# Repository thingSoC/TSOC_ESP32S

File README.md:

# TSOC_ESP32S - thingSoC Wi-Fi Radio Module :

[TSOC_ESP32S](https://github.com/thingSoC/TSOC_ESP32S)

---------------------------------------

## TSOC_ESP32S Status <a name="TSOC_ESP32S_status"/>

**11/06/2016:** 
Revision 1.0 - Initial Layout released to OSHpark

---------------------------------------
## TSOC_ESP32S Model Images

[TSOC_ESP32S](https://github.com/thingSoC/TSOC_ESP32S)

[TSOC_ESP32S](https://github.com/thingSoC/TSOC_ESP32S)

---------------------------------------

## TSOC_ESP32S Documentation Index <a name="TSOC_ESP32S_documentation_index"/>

[TSOC_ESP32S Project](http://thingsoc.github.io/projects/TSOC_ESP32S.html)

[TSOC_ESP32S Hardware](https://github.com/thingSoC/TSOC_ESP32S/tree/master/TSOC_ESP32S/hardware)

---------------------------------------

## thingSoC Documentation Index <a name="thingSoC_documentation_index"/>

[thingSoC Organization Website](http://thingSoC.github.io)

[thingSoC FAQ - Frequently Asked Questions](http://thingsoc.github.io/support/faq.html)

---------------------------------------

[ 
*thingSoC*](http://thingsoc.github.io)

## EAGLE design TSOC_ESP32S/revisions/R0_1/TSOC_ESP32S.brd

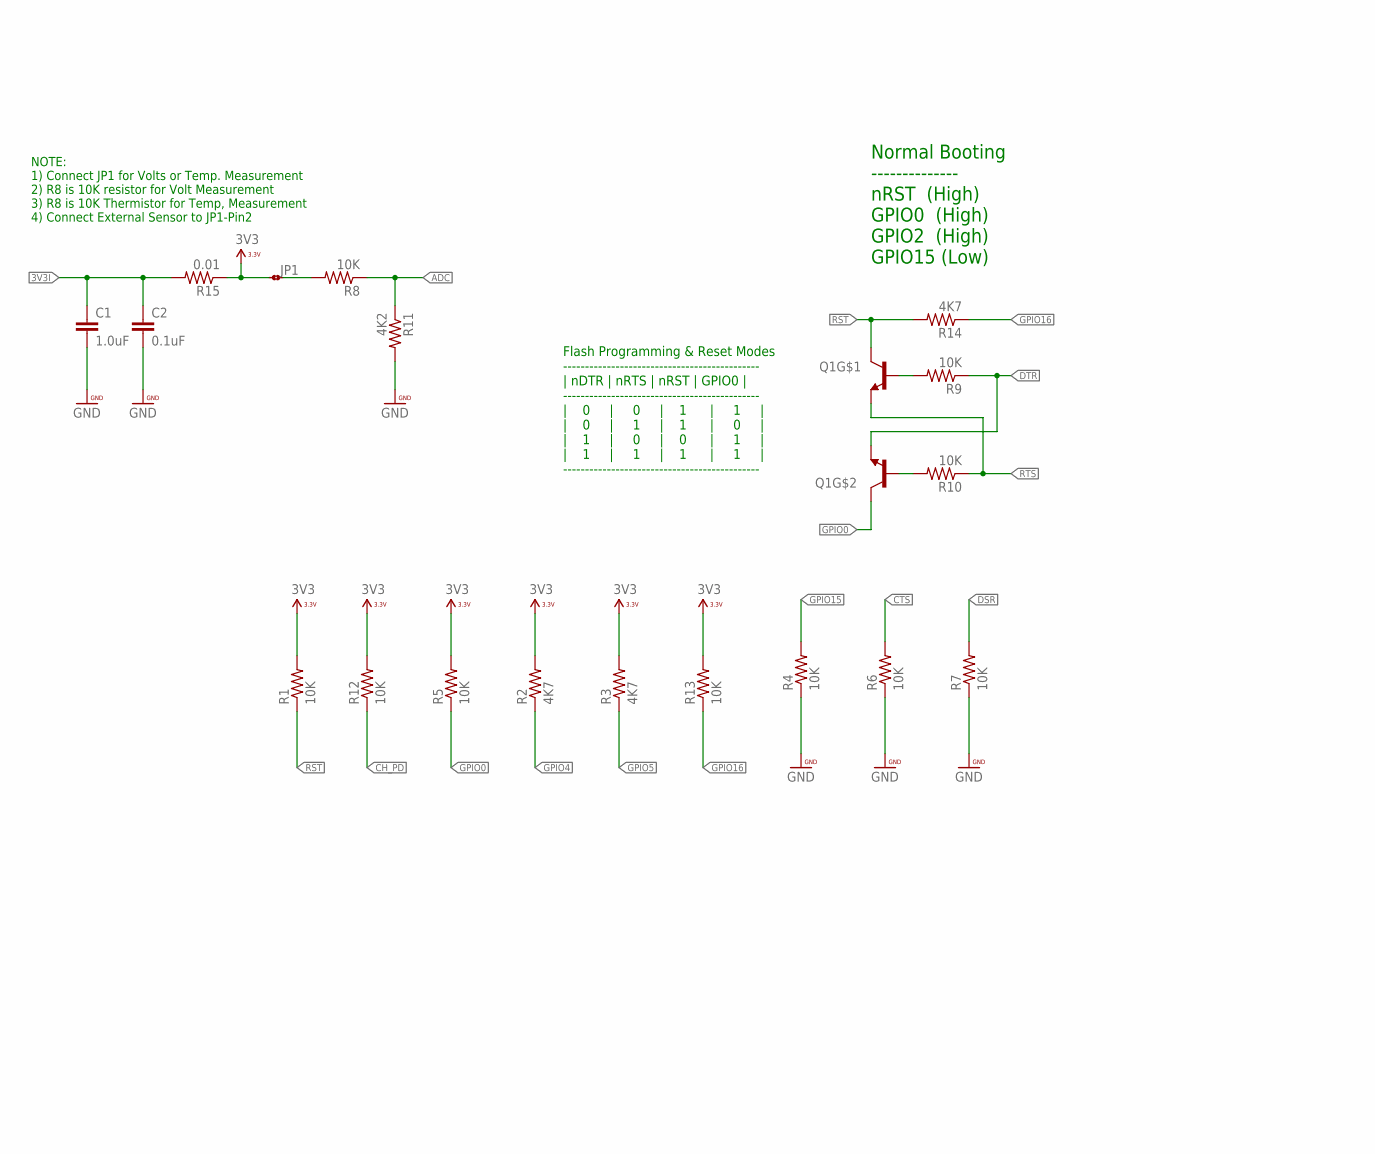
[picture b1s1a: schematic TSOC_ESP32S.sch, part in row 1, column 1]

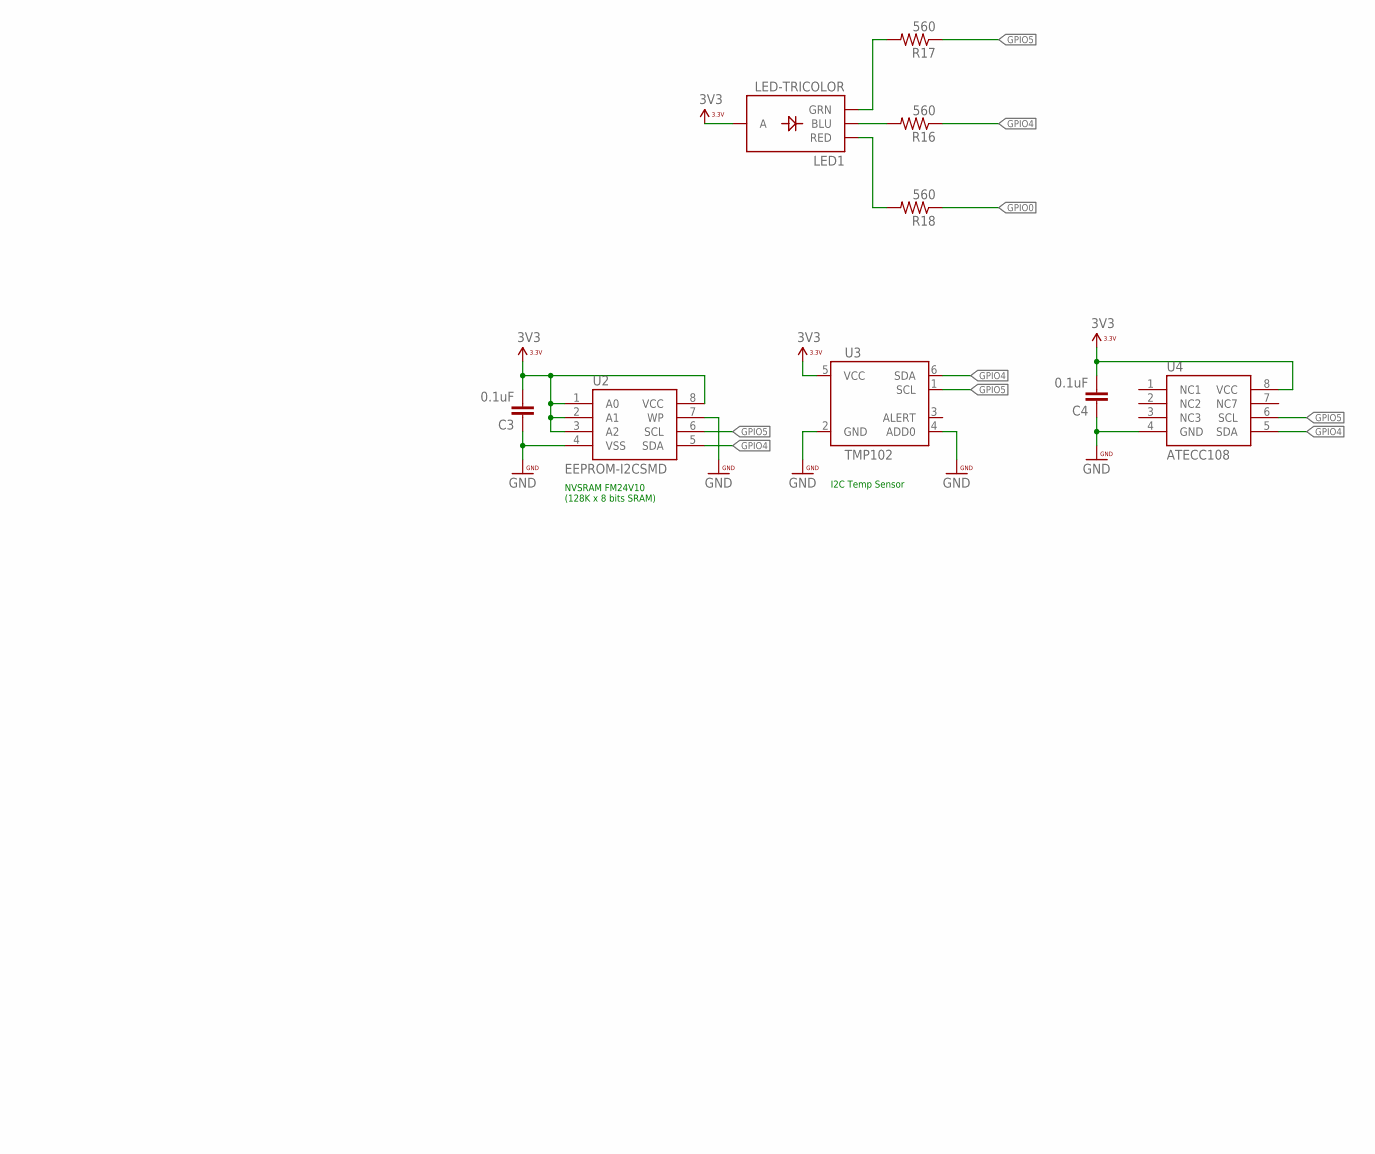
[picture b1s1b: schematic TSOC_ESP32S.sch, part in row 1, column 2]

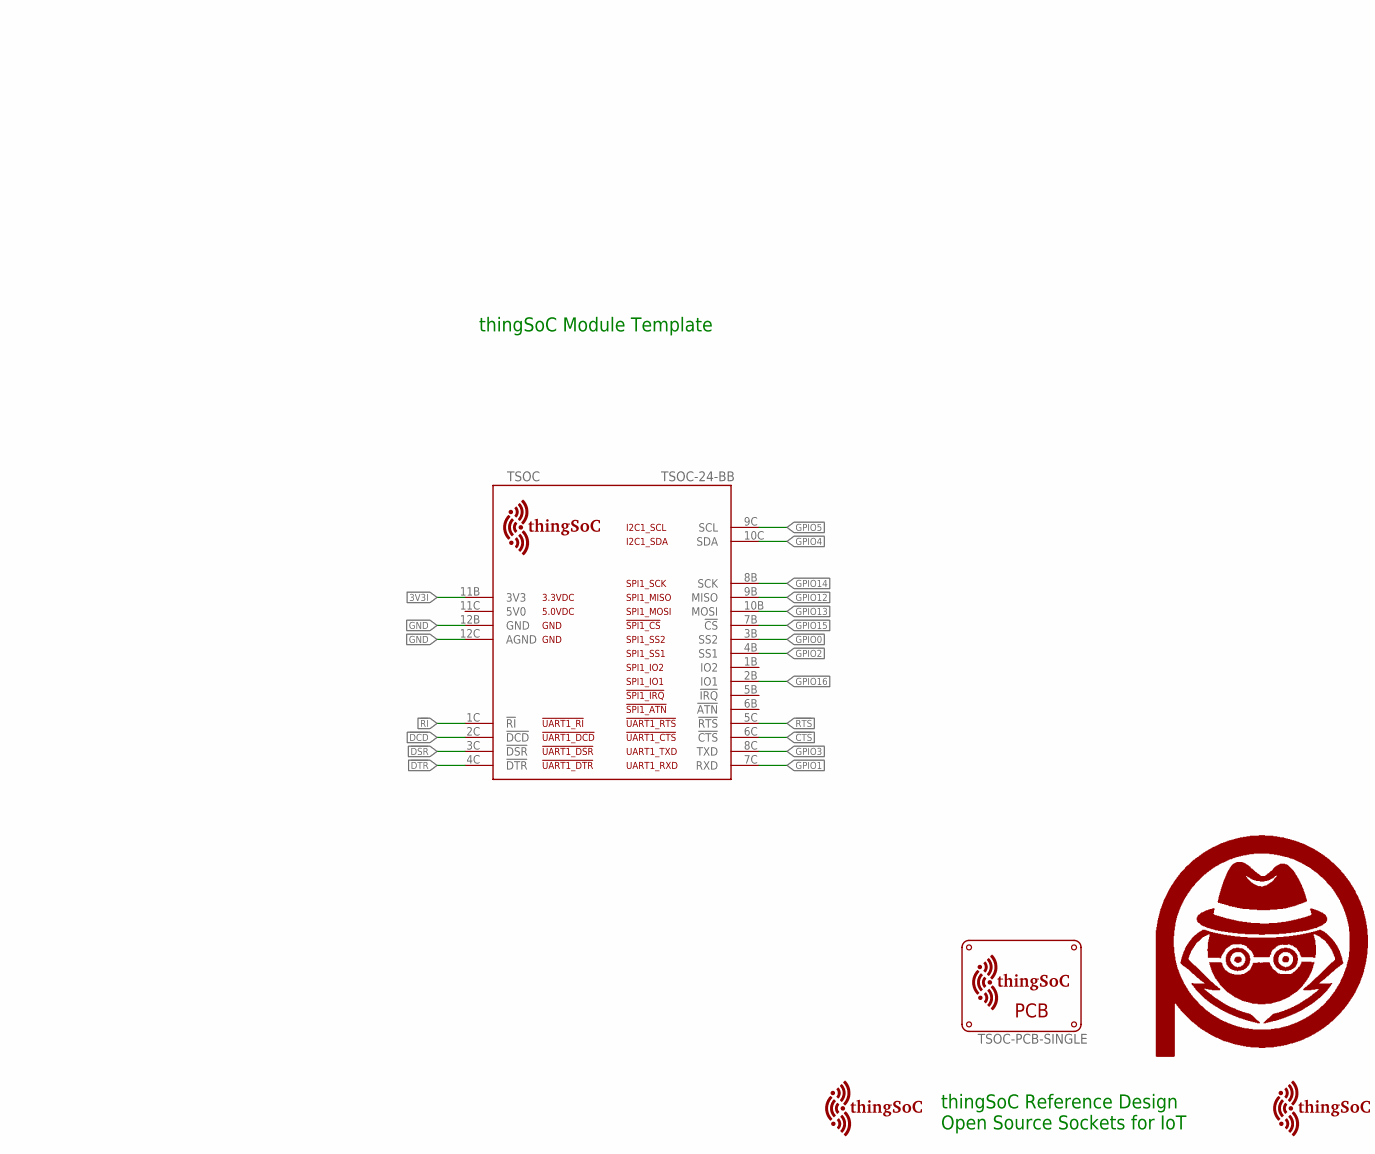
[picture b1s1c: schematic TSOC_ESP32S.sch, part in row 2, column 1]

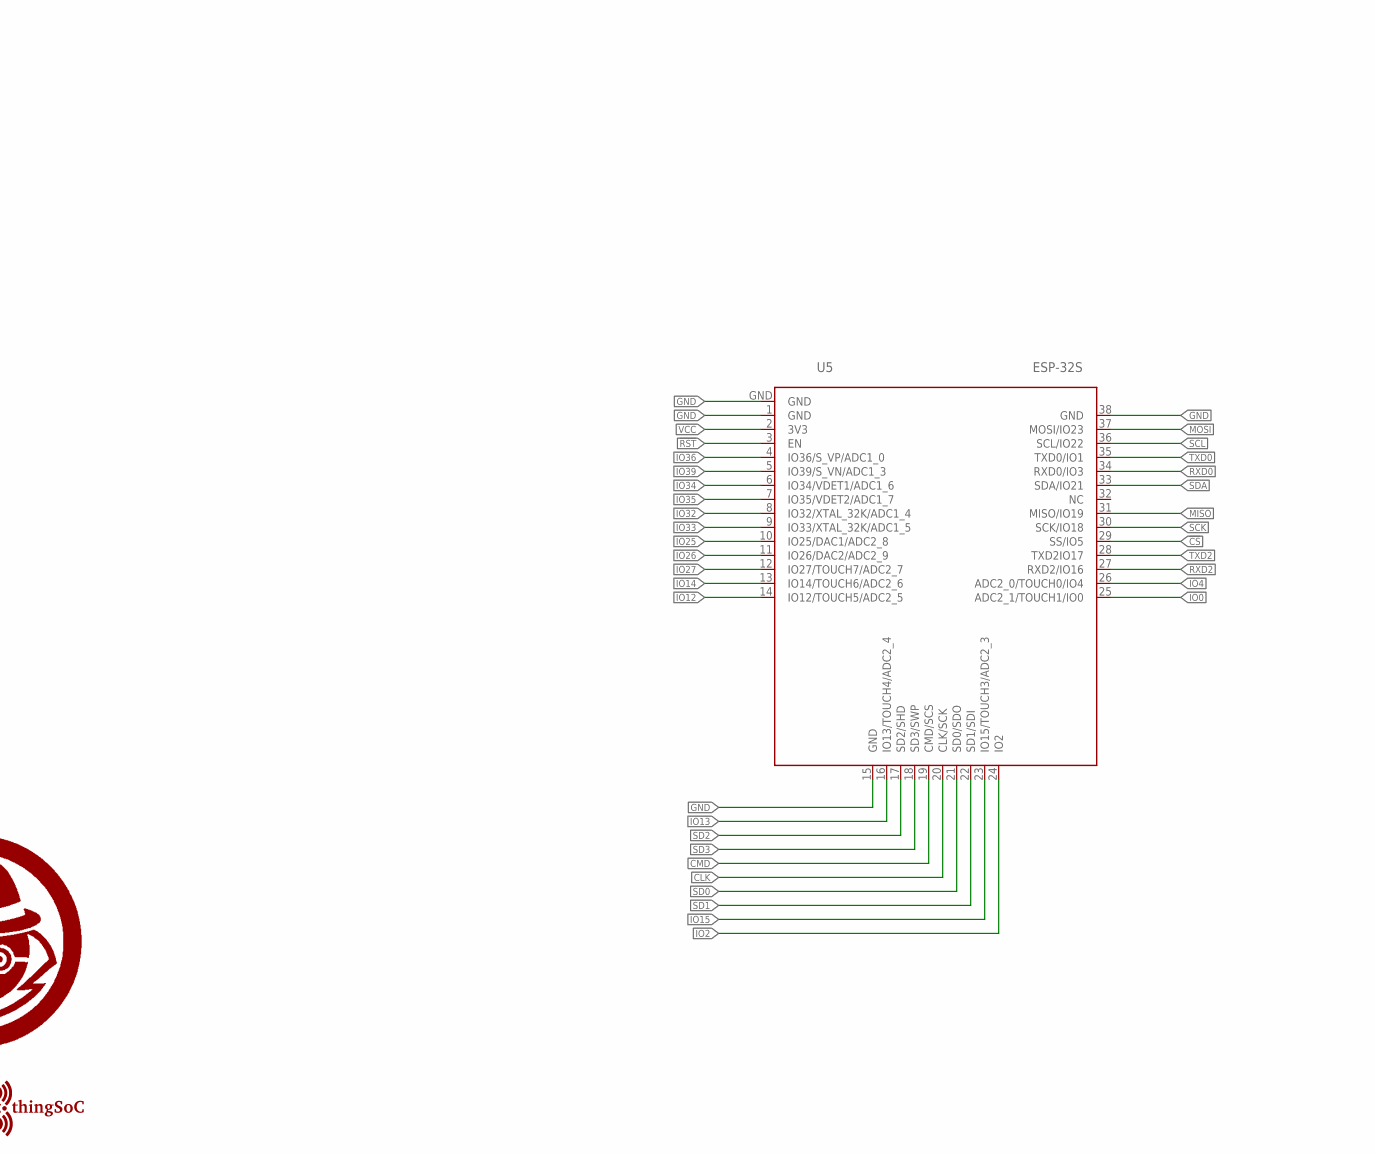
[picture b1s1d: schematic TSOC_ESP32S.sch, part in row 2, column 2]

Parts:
C1: 1.0uF; 0402-CAP
C2, C3, C4: 0.1uF; 0402-CAP
JP1: JMP-2-NO-0402
LED1: LED-TRICOLOR; LED-TRICOLOR-SMD
Q1: MMBT2222A; SOT363
R1, R4, R5, R6, R7, R8, R9, R10, R12, R13: 10K; 0402-RES
R2, R3, R14: 4K7; 0402-RES
R11: 4K2; 0402-RES
R15: 0.01; 0402-RES
R16, R17, R18: 560; 0402-RES
TSOC: TSOC-24-BB; TSOC-BB-S24
U2: EEPROM-I2CSMD; SO08
U3: TMP102; SOT563
U4: ATECC108; SOIC8
U5: ESP-32S
U$11: PA_LOGO_SYMMED; PA_LOGO_AGENT_MED_SYM
U$19, U$20: TSOC-LOGO-MED
U$25: TSOC-PCB-SINGLE; TSOC-BB-BRD-DIM

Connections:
3V3: C3.2, C4.2, JP1.1, LED1.A, R1.2, R2.2, R3.2, R5.2, R12.2, R13.2, R15.1, U2.1 (A0), U2.2 (A1), U2.3 (A2), U2.8 (VCC), U3.5 (VCC), U4.8 (VCC)
3V3I: C1.1, C2.1, R15.2, TSOC.11B (3V3)
!CS: U5.29 (SS/IO5)
!CTS: R6.2, TSOC.6C (!CTS)
!DCD: TSOC.2C (!DCD)
!DSR: R7.2, TSOC.3C (!DSR)
!DTR: Q1.1 (E), R9.1, TSOC.4C (!DTR)
!RI: TSOC.1C (!RI)
!RST: Q1.3 (C), R1.1, R14.2, U5.3 (EN)
!RTS: Q1.4 (E), R10.1, TSOC.5C (!RTS)
ADC: R8.1, R11.1
ADC_RAW: JP1.2, R8.2
BLU: LED1.B (BLU), R16.2
CH_PD: R12.1
CLK: U5.20 (CLK/SCK)
CMD: U5.19 (CMD/SCS)
GND: C1.2, C2.2, C3.1, C4.1, R4.1, R6.1, R7.1, R11.2, TSOC.12B (GND), TSOC.12C (AGND), U2.4 (VSS), U2.7 (WP), U3.2 (GND), U3.4 (ADD0), U4.4 (GND), U5.1 (GND), U5.15 (GND), U5.38 (GND), U5.GND
GPIO0: Q1.6 (C), R5.1, R18.1, TSOC.3B (SS2)
GPIO1: TSOC.7C (RXD)
GPIO2: TSOC.4B (SS1)
GPIO3: TSOC.8C (TXD)
GPIO4: R2.1, R16.1, TSOC.10C (SDA), U2.5 (SDA), U3.6 (SDA), U4.5 (SDA)
GPIO5: R3.1, R17.1, TSOC.9C (SCL), U2.6 (SCL), U3.1 (SCL), U4.6 (SCL)
GPIO12: TSOC.9B (MISO)
GPIO13: TSOC.10B (MOSI)
GPIO14: TSOC.8B (SCK)
GPIO15: R4.2, TSOC.7B (!CS)
GPIO16: R13.1, R14.1, TSOC.2B (IO1)
GRN: LED1.G (GRN), R17.2
IO0: U5.25 (ADC2_1/TOUCH1/IO0)
IO2: U5.24 (IO2)
IO4: U5.26 (ADC2_0/TOUCH0/IO4)
IO12: U5.14 (IO12/TOUCH5/ADC2_5)
IO13: U5.16 (IO13/TOUCH4/ADC2_4)
IO14: U5.13 (IO14/TOUCH6/ADC2_6)
IO15: U5.23 (IO15/TOUCH3/ADC2_3)
IO25: U5.10 (IO25/DAC1/ADC2_8)
IO26: U5.11 (IO26/DAC2/ADC2_9)
IO27: U5.12 (IO27/TOUCH7/ADC2_7)
IO32: U5.8 (IO32/XTAL_32K/ADC1_4)
IO33: U5.9 (IO33/XTAL_32K/ADC1_5)
IO34: U5.6 (IO34/VDET1/ADC1_6)
IO35: U5.7 (IO35/VDET2/ADC1_7)
IO36: U5.4 (IO36/S_VP/ADC1_0)
IO39: U5.5 (IO39/S_VN/ADC1_3)
MISO: U5.31 (MISO/IO19)
MOSI: U5.37 (MOSI/IO23)
unnamed: Q1.5 (B), R9.2
unnamed: Q1.2 (B), R10.2
RED: LED1.R (RED), R18.2
RXD0: U5.34 (RXD0/IO3)
RXD2: U5.27 (RXD2/IO16)
SCK: U5.30 (SCK/IO18)
SCL: U5.36 (SCL/IO22)
SD0: U5.21 (SD0/SDO)
SD1: U5.22 (SD1/SDI)
SD2: U5.17 (SD2/SHD)
SD3: U5.18 (SD3/SWP)
SDA: U5.33 (SDA/IO21)
TXD0: U5.35 (TXD0/IO1)
TXD2: U5.28 (TXD2IO17)
VCC: U5.2 (3V3)

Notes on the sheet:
thingSoC Reference Design Open Source Sockets for IoT
thingSoC Module Template
Normal Booting -------------- nRST (High) GPIO0 (High) GPIO2 (High) GPIO15 (Low)
Flash Programming & Reset Modes --------------------------------------------- | nDTR | nRTS | nRST | GPIO0 | --------------------------------------------- | 0 | 0 | 1 | 1 | | 0 | 1 | 1 | 0 | | 1 | 0 | 0 | 1 | | 1 | 1 | 1 | 1 | ---------------------------------------------
NOTE: 1) Connect JP1 for Volts or Temp. Measurement 2) R8 is 10K resistor for Volt Measurement 3) R8 is 10K Thermistor for Temp, Measurement 4) Connect External Sensor to JP1-Pin2
NVSRAM FM24V10 (128K x 8 bits SRAM)
I2C Temp Sensor

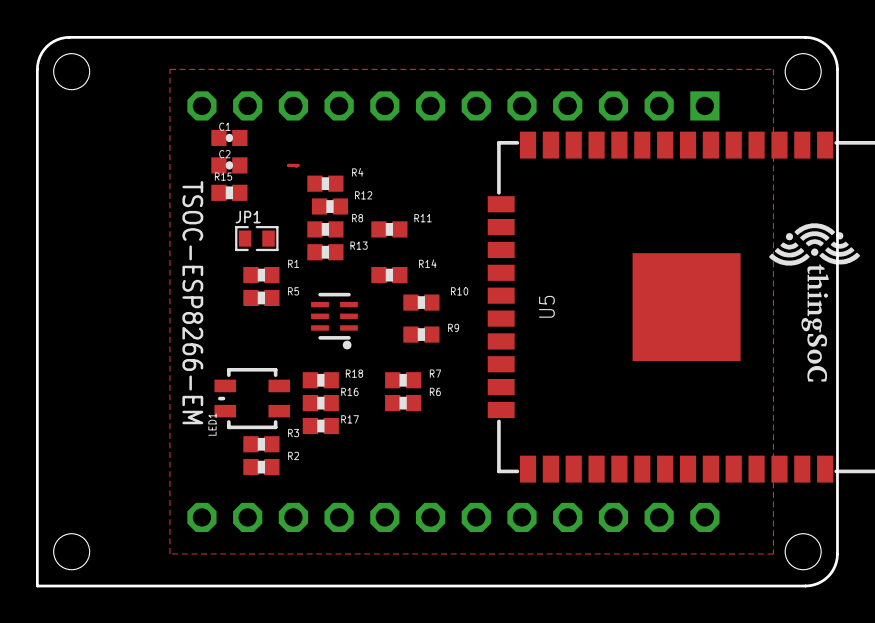
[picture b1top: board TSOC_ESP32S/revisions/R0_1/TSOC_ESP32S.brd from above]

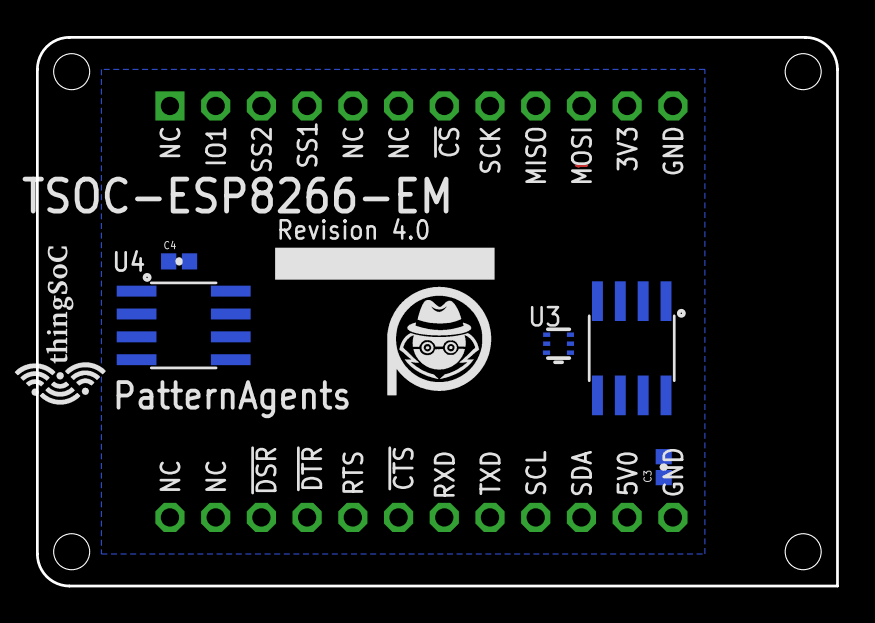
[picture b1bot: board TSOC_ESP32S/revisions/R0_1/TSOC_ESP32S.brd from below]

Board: 2 copper layers, 44.5 x 30.5 mm, 34 parts (7 on the bottom side), 20 nets.

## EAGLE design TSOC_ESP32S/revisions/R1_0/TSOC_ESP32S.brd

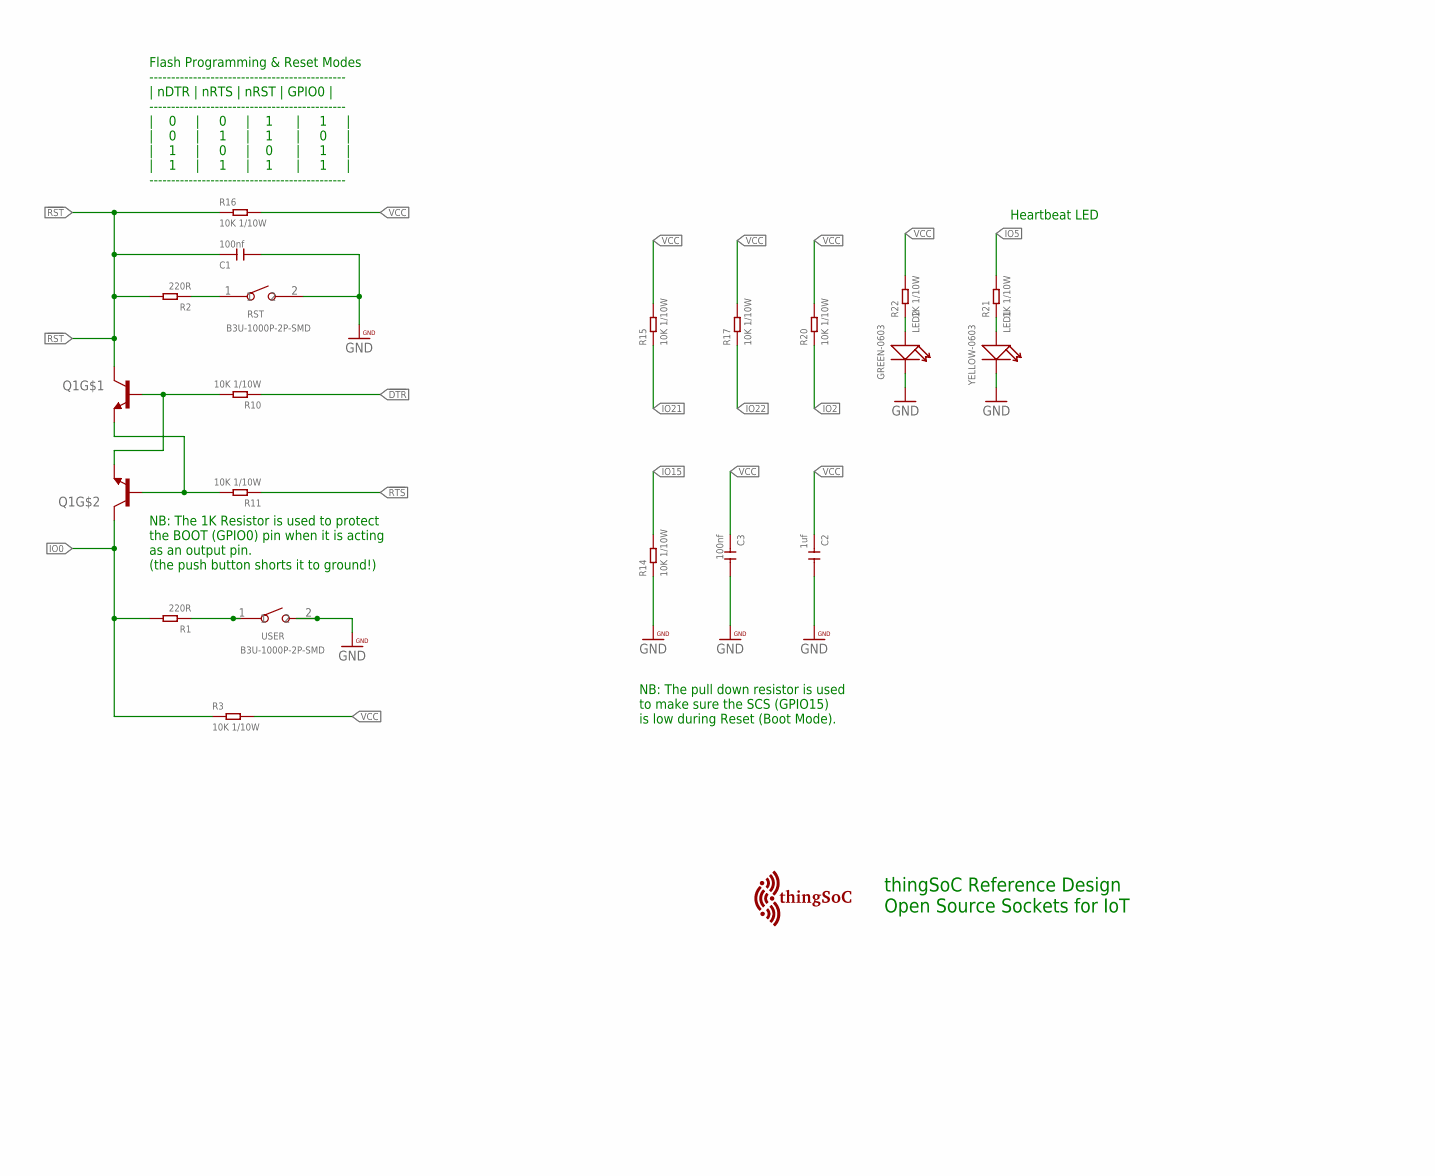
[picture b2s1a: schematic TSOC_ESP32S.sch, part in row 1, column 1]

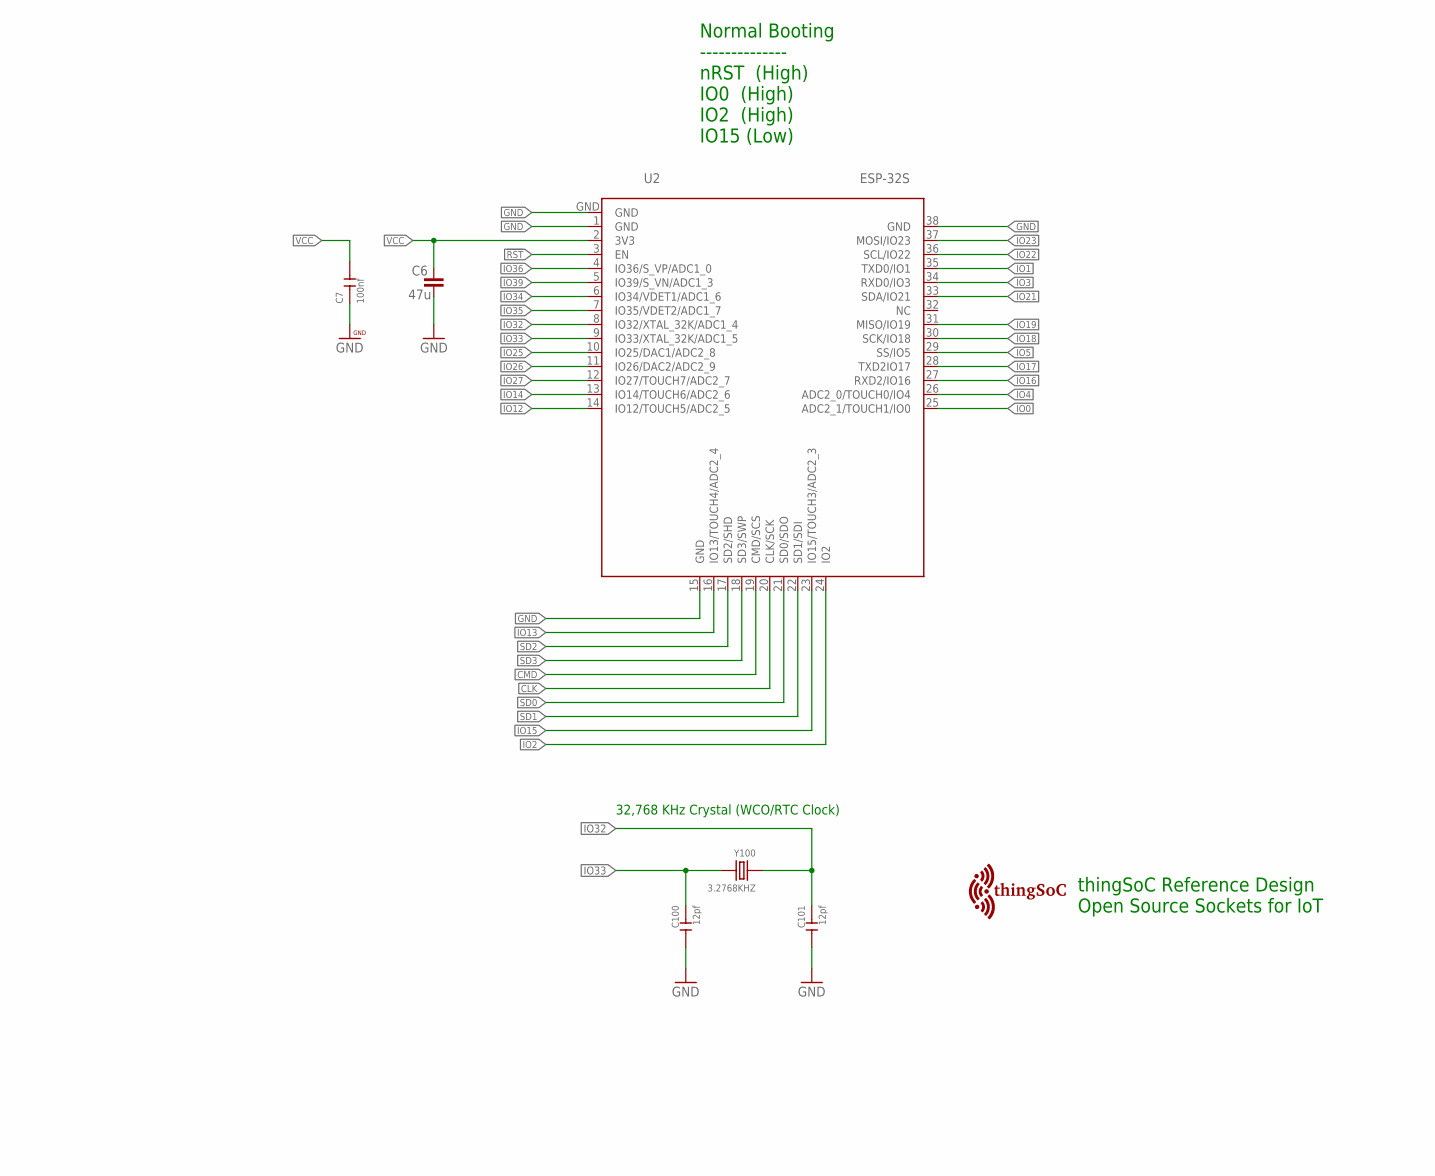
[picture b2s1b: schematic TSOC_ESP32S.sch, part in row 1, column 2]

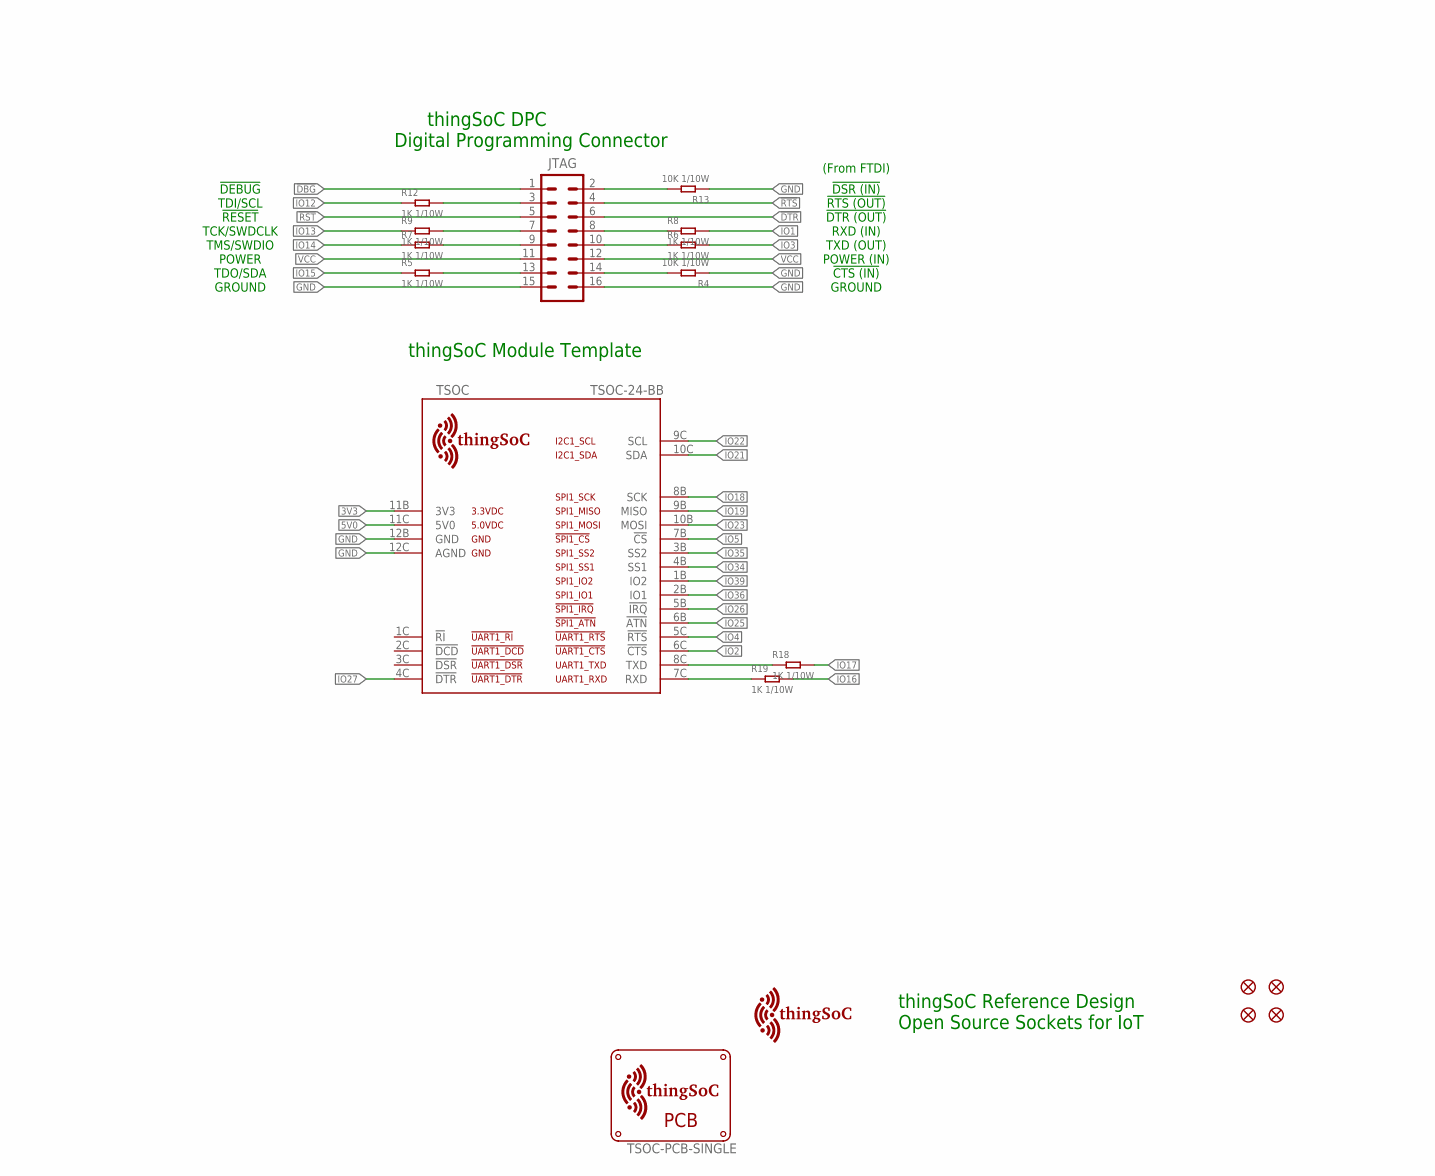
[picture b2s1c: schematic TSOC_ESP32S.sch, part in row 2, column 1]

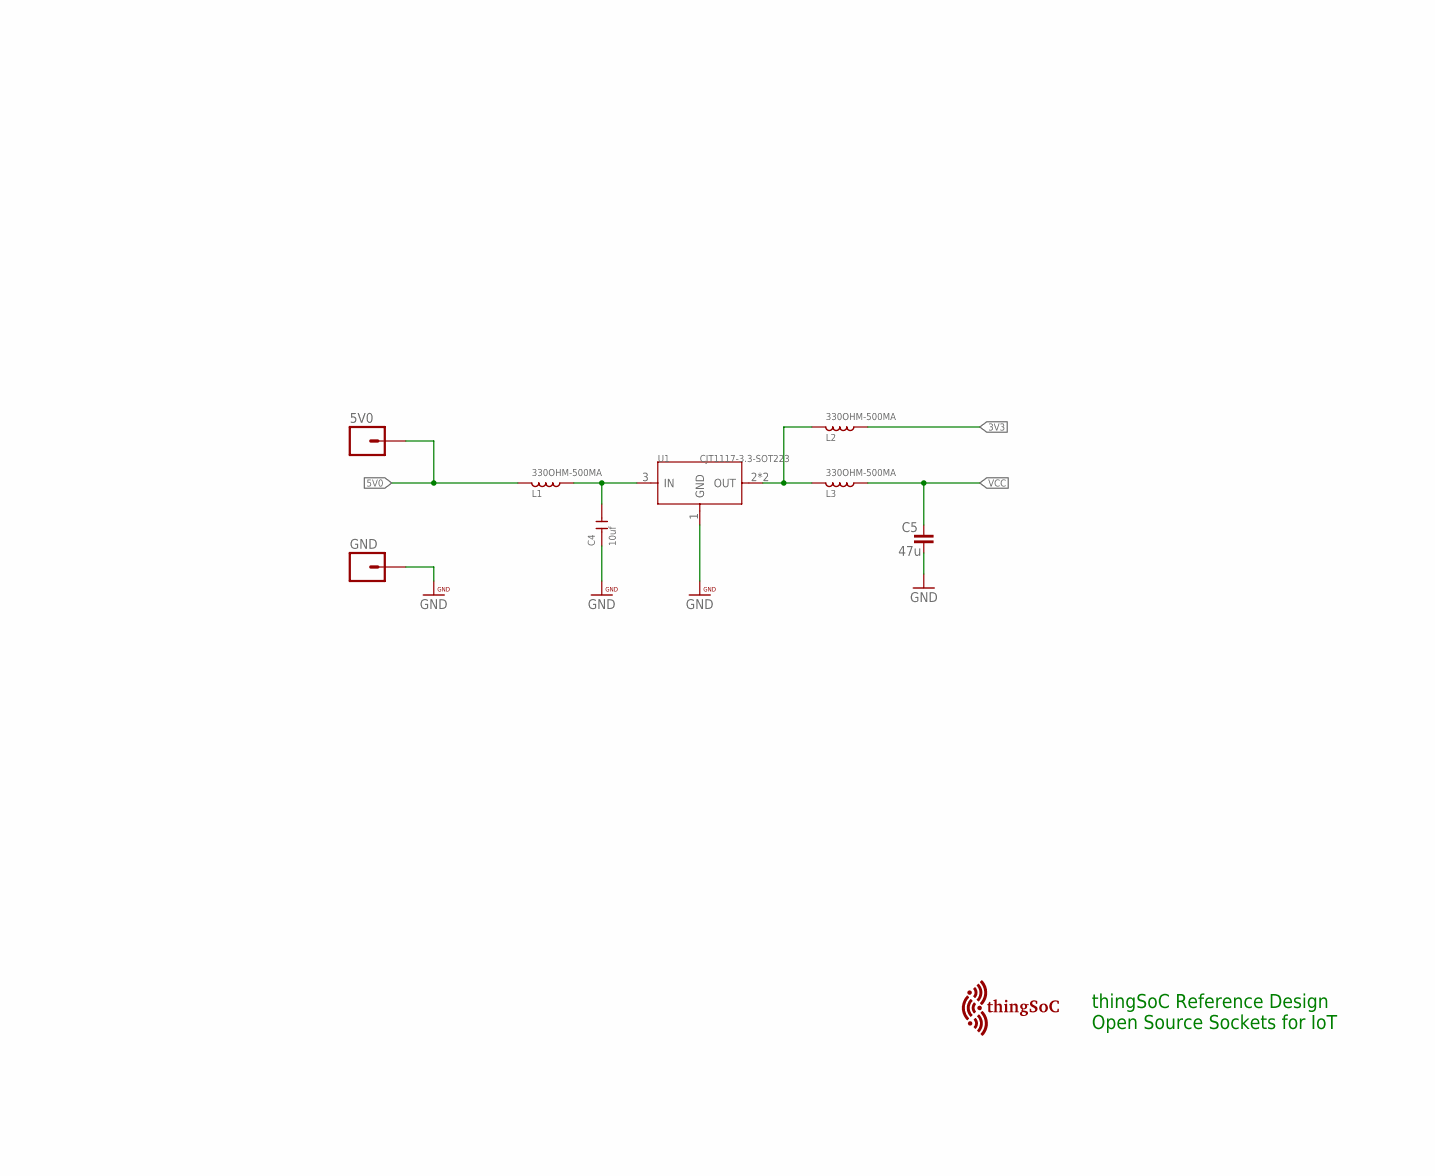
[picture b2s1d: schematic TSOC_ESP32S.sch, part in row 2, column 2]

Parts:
5V0: M01PTH; 1X01
$$U$1, $$U$2: TSOC-LOGO-SMALL; TSOC-LOGO-SML
BRD: TSOC-PCB-SINGLE; TSOC-BB-BRD-DIM
C1, C3, C7: 100nf; C0603
C2: 1uf; C0603
C4: 10uf; C0603
C5, C6: 47u; C1206
C100, C101: 12pf; C0603
FID1, FID2, FID3, FID4: FIDUCIALUFIDUCIAL; MICRO-FIDUCIAL
GND: M01PTH; 1X01
JTAG: M08X2; 2X8
L1, L2, L3: 330OHM-500MA; L0603
LED1: YELLOW-0603; LED-0603
LED2: GREEN-0603; LED-0603
Q1: MMBT2222A; SOT363
R1, R2: 220R; R0603
R3, R4, R10, R11, R13, R14, R15, R16, R17, R20: 10K 1/10W; R0603
R5, R6, R7, R8, R9, R12, R18, R19, R21, R22: 1K 1/10W; R0603
RST: B3U-1000P-2P-SMD; SW2-2.6-3.0X2.5X1.2+0.4MM
TSOC: TSOC-24-BB; TSOC-BB-S24
U1: CJT1117-3.3-SOT223; SOT-223
U2: ESP-32S
U$101: TSOC-LOGO-SMALL; TSOC-LOGO-SML
U$102: TSOC-LOGO-LRG
USER: B3U-1000P-2P-SMD; SW2-2.6-3.0X2.5X1.2+0.4MM
Y100: 3.2768KHZ; X2-SMD-L2.0X1.2X0.55MM

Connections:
3V3: L2.2, TSOC.11B (3V3)
5V: C4.2, L1.2, U1.3 (IN)
5V0: 5V0.1, L1.1, TSOC.11C (5V0)
!CTSE: JTAG.14, R4.2
!DBG: JTAG.1
!DSRE: JTAG.2, R13.2
!DTR: JTAG.6, R10.1
!RST: C1.1, JTAG.5, Q1.3 (C), R2.2, R16.1, U2.3 (EN)
!RTS: JTAG.4, R11.1
CLK: U2.20 (CLK/SCK)
CMD: U2.19 (CMD/SCS)
GND: C1.2, C2.2, C3.2, C4.1, C5.1, C6.1, C7.1, C100.2, C101.2, GND.1, JTAG.15, JTAG.16, LED1.-, LED2.-, R4.1, R13.1, R14.1, RST.2, TSOC.12B (GND), TSOC.12C (AGND), U1.1 (GND), U2.1 (GND), U2.15 (GND), U2.38 (GND), U2.GND, USER.2
IO0: Q1.6 (C), R1.2, R3.1, U2.25 (ADC2_1/TOUCH1/IO0)
IO1: R8.2, U2.35 (TXD0/IO1)
IO1E: JTAG.8, R8.1
IO2: R20.1, TSOC.6C (!CTS), U2.24 (IO2)
IO3: R6.2, U2.34 (RXD0/IO3)
IO3E: JTAG.10, R6.1
IO4: TSOC.5C (!RTS), U2.26 (ADC2_0/TOUCH0/IO4)
IO5: R21.2, TSOC.7B (!CS), U2.29 (SS/IO5)
IO12: R12.1, U2.14 (IO12/TOUCH5/ADC2_5)
IO12E: JTAG.3, R12.2
IO13: R9.1, U2.16 (IO13/TOUCH4/ADC2_4)
IO13E: JTAG.7, R9.2
IO14: R7.1, U2.13 (IO14/TOUCH6/ADC2_6)
IO14E: JTAG.9, R7.2
IO15: R5.1, R14.2, U2.23 (IO15/TOUCH3/ADC2_3)
IO15E: JTAG.13, R5.2
IO16: R19.2, U2.27 (RXD2/IO16)
IO16E: R19.1, TSOC.7C (RXD)
IO17: R18.2, U2.28 (TXD2IO17)
IO17E: R18.1, TSOC.8C (TXD)
IO18: TSOC.8B (SCK), U2.30 (SCK/IO18)
IO19: TSOC.9B (MISO), U2.31 (MISO/IO19)
IO21: R15.1, TSOC.10C (SDA), U2.33 (SDA/IO21)
IO22: R17.1, TSOC.9C (SCL), U2.36 (SCL/IO22)
IO23: TSOC.10B (MOSI), U2.37 (MOSI/IO23)
IO25: TSOC.6B (!ATN), U2.10 (IO25/DAC1/ADC2_8)
IO26: TSOC.5B (!IRQ), U2.11 (IO26/DAC2/ADC2_9)
IO27: TSOC.4C (!DTR), U2.12 (IO27/TOUCH7/ADC2_7)
IO32: C101.1, U2.8 (IO32/XTAL_32K/ADC1_4), Y100.1
IO33: C100.1, U2.9 (IO33/XTAL_32K/ADC1_5), Y100.2
IO34: TSOC.4B (SS1), U2.6 (IO34/VDET1/ADC1_6)
IO35: TSOC.3B (SS2), U2.7 (IO35/VDET2/ADC1_7)
IO36: TSOC.2B (IO1), U2.4 (IO36/S_VP/ADC1_0)
IO39: TSOC.1B (IO2), U2.5 (IO39/S_VN/ADC1_3)
unnamed: LED1.+, R21.1
unnamed: R1.1, USER.1
unnamed: R2.1, RST.1
unnamed: LED2.+, R22.1
RES: Q1.1 (E), Q1.5 (B), R10.2
ROS: Q1.2 (B), Q1.4 (E), R11.2
SD0: U2.21 (SD0/SDO)
SD1: U2.22 (SD1/SDI)
SD2: U2.17 (SD2/SHD)
SD3: U2.18 (SD3/SWP)
VCC: C2.1, C3.1, C5.2, C6.2, C7.2, JTAG.11, JTAG.12, L3.2, R3.2, R15.2, R16.2, R17.2, R20.2, R22.2, U2.2 (3V3)
VOUT: L2.1, L3.1, U1.2 (OUT), U1.TER (OUT)

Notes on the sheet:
Heartbeat LED
thingSoC Reference Design Open Source Sockets for IoT
TDO/SDA
TDI/SCL
!RESET
TCK/SWDCLK
TMS/SWDIO
POWER
GROUND
!DEBUG
!DSR (IN)
!RTS (OUT)
!CTS (IN)
!DTR (OUT)
TXD (OUT)
RXD (IN)
POWER (IN)
thingSoC DPC Digital Programming Connector
Normal Booting -------------- nRST (High) IO0 (High) IO2 (High) IO15 (Low)
thingSoC Module Template
Flash Programming & Reset Modes --------------------------------------------- | nDTR | nRTS | nRST | GPIO0 | --------------------------------------------- | 0 | 0 | 1 | 1 | | 0 | 1 | 1 | 0 | | 1 | 0 | 0 | 1 | | 1 | 1 | 1 | 1 | ---------------------------------------------
NB: The 1K Resistor is used to protect the BOOT (GPIO0) pin when it is acting as an output pin. (the push button shorts it to ground!)
NB: The pull down resistor is used to make sure the SCS (GPIO15) is low during Reset (Boot Mode).
(From FTDI)
32,768 KHz Crystal (WCO/RTC Clock)

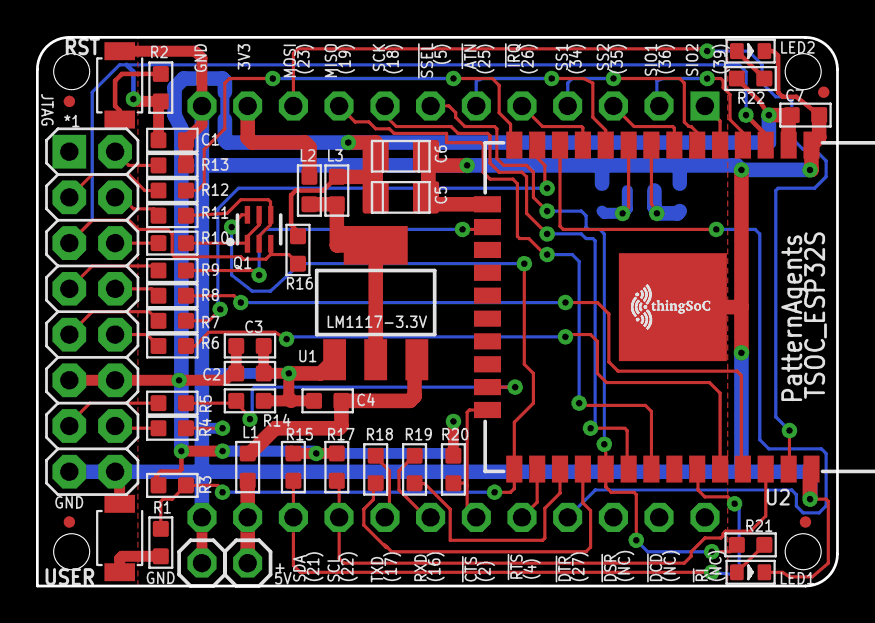
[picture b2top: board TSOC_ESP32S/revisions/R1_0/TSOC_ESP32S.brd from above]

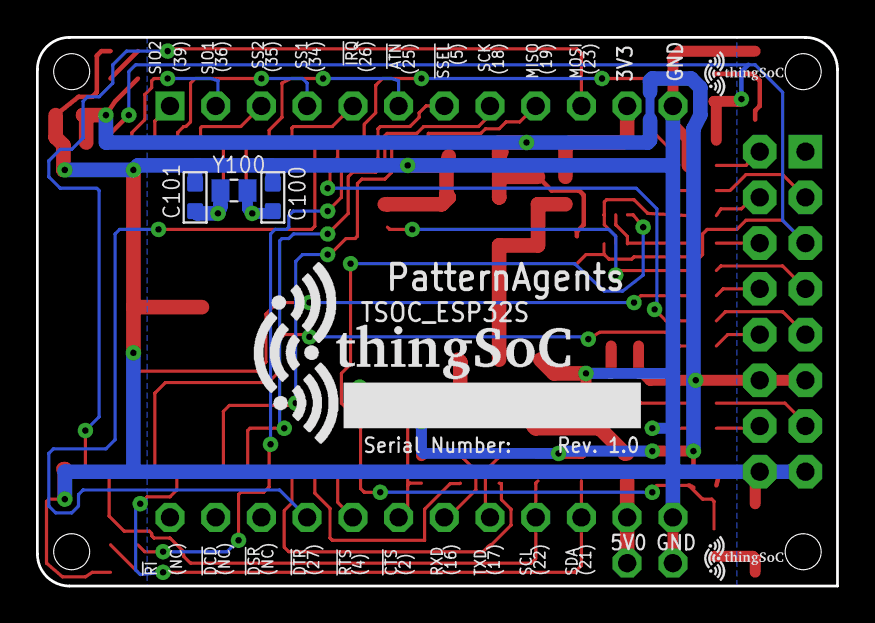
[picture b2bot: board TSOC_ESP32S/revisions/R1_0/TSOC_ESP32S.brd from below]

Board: 2 copper layers, 44.5 x 30.5 mm, 56 parts (6 on the bottom side), 51 nets.

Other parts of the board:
U$100: TSOC-LOGO-SMALL; TSOC-LOGO-SML

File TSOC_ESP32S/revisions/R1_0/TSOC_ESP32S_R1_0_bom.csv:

"Part";"Value";"Device";"Package";"Description";"";
"5V0";"";"M01PTH";"1X01";"Header 1";"";
"C1";"100nf";"CERAMIC-100NF-50V-10%-X7R(0603)";"C0603";"302010138";"";
"C2";"1uf";"CERAMIC-1UF-25V-10%-X7R(0603)";"C0603";"302010139";"";
"C3";"100nf";"CERAMIC-100NF-50V-10%-X7R(0603)";"C0603";"302010138";"";
"C4";"10uf";"CERAMIC-10UF-10V-10%-X5R(0603)";"C0603";"302010103";"";
"C5";"47u";"CAPACITOR-1206";"C1206";"Capacitors";"";
"C6";"47u";"CAPACITOR-1206";"C1206";"Capacitors";"";
"C7";"100nf";"CERAMIC-10UF-10V-10%-X5R(0603)";"C0603";"302010103";"";
"C100";"12pf";"CERAMIC-12PF-50V-5%-NPO(0603)";"C0603";"302010067";"";
"C101";"12pf";"CERAMIC-12PF-50V-5%-NPO(0603)";"C0603";"302010067";"";
"GND";"";"M01PTH";"1X01";"Header 1";"";
"JTAG";"";"M08X2";"2X8";".1" headers, two rows of 8 each";"";
"L1";"330OHM-500MA";"SMD-FERRITE-CHIP-120-OHM-500MA(0603)";"L0603";"303030001";"";
"L2";"330OHM-500MA";"SMD-FERRITE-CHIP-120-OHM-500MA(0603)";"L0603";"303030001";"";
"L3";"330OHM-500MA";"SMD-FERRITE-CHIP-120-OHM-500MA(0603)";"L0603";"303030001";"";
"LED1";"YELLOW-0603";"SMD-LED-CLEAR-YELLOW(0603)";"LED-0603";"304090044";"";
"LED2";"GREEN-0603";"SMD-LED-CLEAR-GREEN(0603)";"LED-0603";"304090043";"";
"Q1";"MMBT2222A";"MMDT3904";"SOT363";"Dual NPN transistor";"";
"R1";"220R";"SMD-RES-220R-5%-1/10W(0603)";"R0603";"301010163";"";
"R2";"220R";"SMD-RES-220R-5%-1/10W(0603)";"R0603";"301010163";"";
"R3";"10K 1/10W";"SMD-RES-10K-5%-1/10W(0603)";"R0603";"301010293";"";
"R4";"10K 1/10W";"SMD-RES-10K-5%-1/10W(0603)";"R0603";"301010293";"";
"R5";"1K 1/10W";"SMD-RES-1K-5%-1/10W(0603)";"R0603";"301010291";"";
"R6";"1K 1/10W";"SMD-RES-1K-5%-1/10W(0603)";"R0603";"301010291";"";
"R7";"1K 1/10W";"SMD-RES-1K-5%-1/10W(0603)";"R0603";"301010291";"";
"R8";"1K 1/10W";"SMD-RES-1K-5%-1/10W(0603)";"R0603";"301010291";"";
"R9";"1K 1/10W";"SMD-RES-1K-5%-1/10W(0603)";"R0603";"301010291";"";
"R10";"10K 1/10W";"SMD-RES-10K-5%-1/10W(0603)";"R0603";"301010293";"";
"R11";"10K 1/10W";"SMD-RES-10K-5%-1/10W(0603)";"R0603";"301010293";"";
"R12";"1K 1/10W";"SMD-RES-1K-5%-1/10W(0603)";"R0603";"301010291";"";
"R13";"10K 1/10W";"SMD-RES-10K-5%-1/10W(0603)";"R0603";"301010293";"";
"R14";"10K 1/10W";"SMD-RES-10K-5%-1/10W(0603)";"R0603";"301010293";"";
"R15";"10K 1/10W";"SMD-RES-10K-5%-1/10W(0603)";"R0603";"301010293";"";
"R16";"10K 1/10W";"SMD-RES-10K-5%-1/10W(0603)";"R0603";"301010293";"";
"R17";"10K 1/10W";"SMD-RES-10K-5%-1/10W(0603)";"R0603";"301010293";"";
"R18";"1K 1/10W";"SMD-RES-1K-5%-1/10W(0603)";"R0603";"301010291";"";
"R19";"1K 1/10W";"SMD-RES-1K-5%-1/10W(0603)";"R0603";"301010291";"";
"R20";"10K 1/10W";"SMD-RES-10K-5%-1/10W(0603)";"R0603";"301010293";"";
"R21";"1K 1/10W";"SMD-RES-1K-5%-1/10W(0603)";"R0603";"301010291";"";
"R22";"1K 1/10W";"SMD-RES-1K-5%-1/10W(0603)";"R0603";"301010291";"";
"RST";"B3U-1000P-2P-SMD";"SMD-BUTTON(2P-3.0X2.5X1.2+0.4MM)-B3U-1000P-2P-SMD";"SW2-2.6-3.0X2.5X1.2+0.4MM";"311020047";"";
"U1";"CJT1117-3.3-SOT223";"PMIC-CJT1117-3.3(SOT223)";"SOT-223";"310030097";"";
"U2";"ESP-32S";"ESP-32S";"ESP-32S";"";"";
"USER";"B3U-1000P-2P-SMD";"SMD-BUTTON(2P-3.0X2.5X1.2+0.4MM)-B3U-1000P-2P-SMD";"SW2-2.6-3.0X2.5X1.2+0.4MM";"311020047";"";
"Y100";"3.2768KHZ";"SMD-CRYSTAL-32.768KHZ-12.5PF-20PPM-90K(2P-L2.0X1.2MM)";"X2-SMD-L2.0X1.2X0.55MM";"306010020";"";

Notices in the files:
parts and their libraries:
PatternAgents-ProtoPads: License : http://creativecommons.org/licenses/by-sa/4.0
(Creative Commons 4.0)
SparkFun-DiscreteSemi: Licensing: Creative Commons ShareAlike 4.0 International - https://creativecommons.org/licenses/by-sa/4.0
